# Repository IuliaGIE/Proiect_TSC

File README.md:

# DeskAssistant v15 – ESP32-C6 Smart E-Ink Device

## 🔧 Diagrama bloc

---

## 📦 Bill of Materials (BOM)

| Componentă | Link Mouser | Link Comet | Datasheet |
|------------|-------------|------------|-----------|
| ESP32-C6-WROOM-1 | [Mouser](https://www.mouser.com/ProductDetail/356-ESP32C6WRM1) | [Comet](https://www.comet.bg/en/products/44639/) | [Datasheet ESP32-C6](https://www.espressif.com/sites/default/files/documentation/esp32-c6_datasheet_en.pdf) |
| BME688 | [Mouser](https://www.mouser.com/ProductDetail/Bosch-Sensortec/BME688) | [Comet](https://www.comet.bg/en/products/43883/) | [Datasheet BME688](https://www.bosch-sensortec.com/media/boschsensortec/downloads/datasheets/bst-bme688-ds001.pdf) |
| MAX17048 | [Mouser](https://www.mouser.com/ProductDetail/Maxim-Integrated/MAX17048G+) | [Comet](https://www.comet.bg/en/products/40714/) | [Datasheet MAX17048](https://datasheets.maximintegrated.com/en/ds/MAX17048-MAX17049.pdf) |
| MCP73831 (Battery Charger) | [Mouser](https://www.mouser.com/ProductDetail/Microchip-Technology/MCP73831T-2ACIOT) | [Comet](https://www.comet.bg/en/products/43632/) | [Datasheet MCP73831](https://ww1.microchip.com/downloads/en/DeviceDoc/20001984g.pdf) |
| DS3231 RTC | [Mouser](https://www.mouser.com/ProductDetail/Maxim-Integrated/DS3231SN) | [Comet](https://www.comet.bg/en/products/38983/) | [Datasheet DS3231](https://datasheets.maximintegrated.com/en/ds/DS3231.pdf) |
| 7.5" E-Ink Display (WSH-13187) | [Mouser](https://www.mouser.com/ProductDetail/Waveshare/WSH-13187) | [Comet](https://www.comet.bg/en/products/45670/) | [Datasheet E-Ink](https://www.waveshare.com/w/upload/0/09/7.5inch-e-paper-b-specification.pdf) |
| LDO 3.3V | [Mouser](https://www.mouser.com/ProductDetail/Texas-Instruments/LP2985AIM5-33) | [Comet](https://www.comet.bg/en/products/43540/) | [Datasheet LDO](https://www.ti.com/lit/ds/symlink/lp2985.pdf) |
| SD Card Socket | [Mouser](https://www.mouser.com/ProductDetail/Amphenol/101-00594-68) | [Comet](https://www.comet.bg/en/products/37655/) | [Datasheet Socket](https://cdn.amphenol-icc.com/media/wysiwyg/files/drawing/10100594681.pdf) |
| LiPo Battery 2500mAh | [Mouser](https://www.mouser.com/ProductDetail/Adafruit/328) | [Comet](https://www.comet.bg/en/products/37491/) | [Specificații](https://cdn-shop.adafruit.com/datasheets/328.pdf) |

---

## 🧠 Funcționalitate Hardware

DeskAssistant v15 este un dispozitiv portabil cu ecran E-Ink, destinat afișării de informații de mediu, oră și nivel baterie. Este alimentat fie prin USB-C, fie dintr-o baterie LiPo de 2500 mAh.

### Flux de alimentare:
- Portul USB-C oferă 5V către MCP73831, care încarcă bateria LiPo.
- Tensiunea de 3.7V de la baterie este convertită de un LDO în 3.3V, alimentând toate componentele.
- Monitorizarea bateriei este realizată cu MAX17048.

### Senzori și afișaj:
- Temperatura, umiditatea, presiunea și compușii volatili (VOC) sunt măsurați cu senzorul BME688 prin magistrala I2C.
- RTC-ul DS3231 furnizează ora exactă, tot prin I2C.
- Afișajul E-Ink de 7.5 inch este conectat prin SPI și oferă un consum redus de energie.
- Datele pot fi salvate pe un card microSD (SPI).
- Trei butoane conectate pe GPIO sunt utilizate pentru controlul interfeței.

### Calcul estimativ consum:
- ESP32-C6: ~20mA în idle, ~200mA în Wi-Fi TX
- E-Ink: consum doar în actualizare (~26mA)
- BME688: ~2.1mA în mod activ
- RTC: ~1.5μA
- MAX17048: ~50μA
- Autonomie estimată: ~30-40 ore în regim normal, cu Wi-Fi ocazional

---

## 📌 Maparea pinilor ESP32-C6

| Componentă | Pin ESP32-C6 | Interfață | Motivare |
|------------|---------------|-----------|----------|
| E-Ink Display | GPIO4 (MOSI), GPIO5 (MISO), GPIO6 (SCK), GPIO7 (CS), GPIO8 (DC), GPIO9 (RST), GPIO10 (BUSY) | SPI | Control complet al ecranului |
| SD Card | GPIO11 (CS2) | SPI (partajat) | Acces la stocare externă |
| BME688 | GPIO18 (SDA), GPIO19 (SCL) | I2C | Măsurători ambientale |
| MAX17048 | GPIO18 (SDA), GPIO19 (SCL) | I2C | Nivel baterie |
| DS3231 RTC | GPIO18 (SDA), GPIO19 (SCL) | I2C | Ceas exact |
| Butoane | GPIO21, GPIO22, GPIO23 | GPIO IN | Control manual |
| USB-C | GPIO20 (USB D+), GPIO21 (USB D-) | USB-Serial | Flash & debug |
| LED status | GPIO2 | GPIO OUT | Indicație vizuală |

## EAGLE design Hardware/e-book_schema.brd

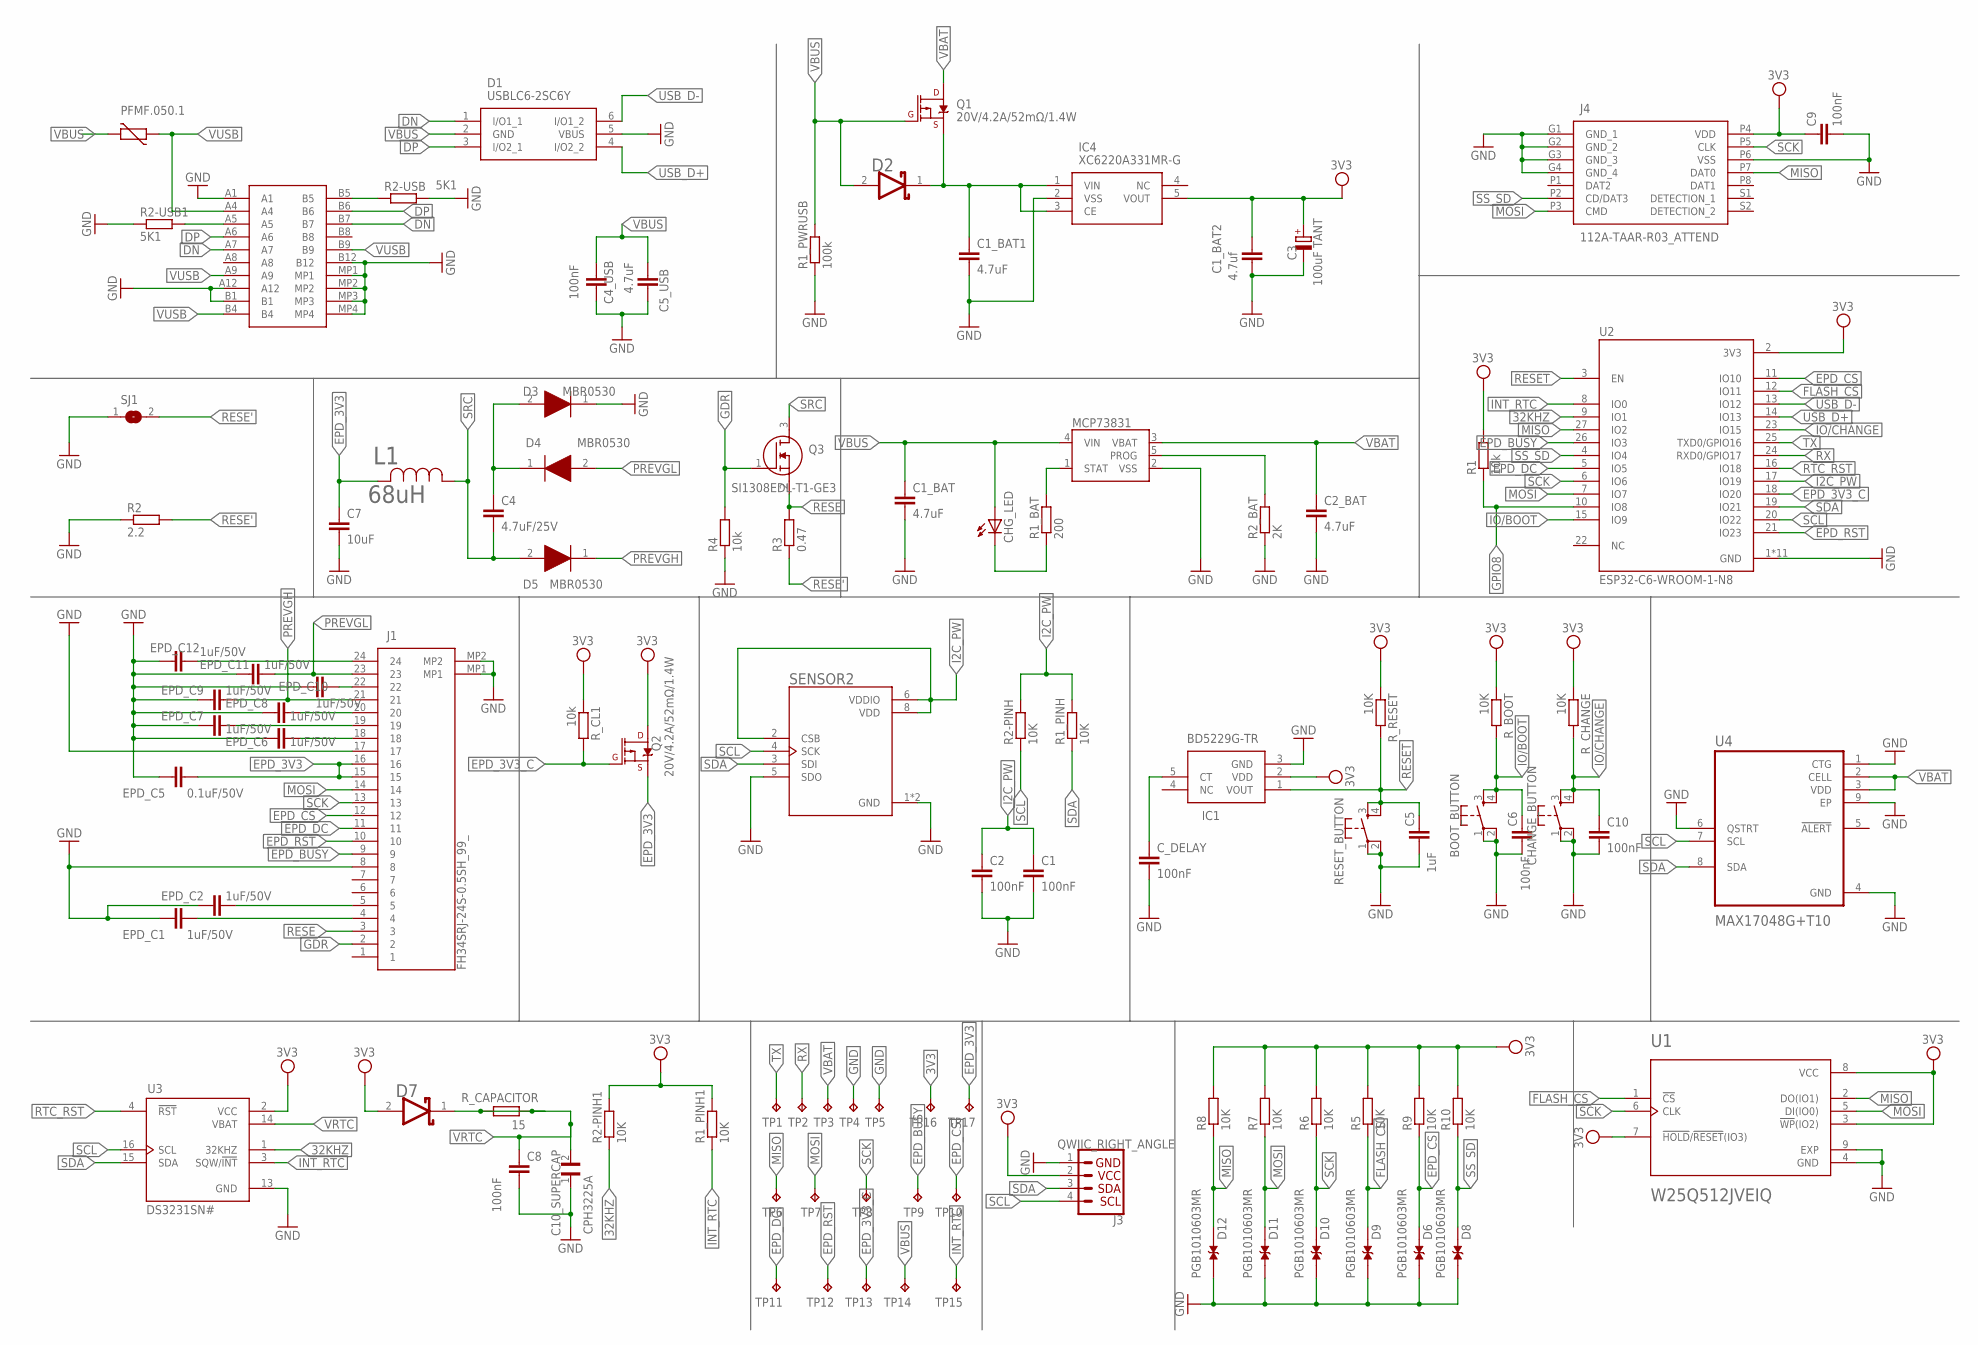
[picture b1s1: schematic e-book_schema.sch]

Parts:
BOOT_BUTTON: BUTTON_CUSYOMV1; MYBUTTON
C1, C2, C4_USB, C6, C8, C9, C10: 100nF; EAGLE-LTSPICE_C0402
C1_BAT, C1_BAT1, C2_BAT, C5_USB: 4.7uF; EAGLE-LTSPICE_C0402
C1_BAT2: 4.7uf; EAGLE-LTSPICE_C0402
C3: 100uF TANT; RCL_CT3528
C4: 4.7uF/25V; EAGLE-LTSPICE_C0402
C5: 1uF; EAGLE-LTSPICE_C0402
C7: 10uF; EAGLE-LTSPICE_C0402
C10_SUPERCAP: CPH3225A; CAPCP3225X100N
CHANGE_BUTTON: BUTTON_CUSYOMV1; MYBUTTON
CHG_LED: ADAFRUIT_LEDCHIP-LED0603; ADAFRUIT_CHIP-LED0603
C_DELAY: 100nF; EAGLE-LTSPICE_C0402
D1: USBLC6-2SC6Y; SOT95P280X145-6N
D2, D7: ESP32_WROVER_AVX---SD0805S020S1R0_AVX_SD0805S020S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; ESP32_WROVER_AVX---SD0805S020S1R0_AVX_SD0805S020S1R0_0
D3, D4, D5: MBR0530; SOD3716X135N
D6, D8, D9, D10, D11, D12: PGB1010603MR; DIOC1608X36N
EPD_C1, EPD_C2, EPD_C6, EPD_C7, EPD_C8, EPD_C9, EPD_C10, EPD_C11, EPD_C12: 1uF/50V; EAGLE-LTSPICE_C0402
EPD_C5: 0.1uF/50V; EAGLE-LTSPICE_C0402
IC1: BD5229G-TR; SOT95P280X125-5N
IC4: XC6220A331MR-G; SOT95P280X120-5N
J1: FH34SRJ-24S-0.5SH_99_; FH34SRJ24S05SH99
J2: SAMACSYS_PARTS_USB4110-GF-A; SAMACSYS_PARTS_USB4110GFA
J3: QWIIC_RIGHT_ANGLE; JST04_1MM_RA
J4: 112A-TAAR-R03_ATTEND; 112ATAARR03ATTEND
L1: 68uH; IND_4828-WE-TPC_WRE
MCP73831: ESP32_WROVER_SPARKFUN-IC-POWER_MCP73831; ESP32_WROVER_SPARKFUN-IC-POWER_SOT23-5
PFMF.050.1: ESP32C6_VARISTORCN1812; ESP32C6_VARISTOR_CT/CN1812
Q1, Q2: 20V/4.2A/52mΩ/1.4W; ESP32_WROVER_SPARKFUN-DISCRETESEMI_SOT23-3
Q3: SI1308EDL-T1-GE3; SOT65P210X110-3N
R1, R4: 10k; ESP32_WROVER_EAGLE-LTSPICE_R0402
R1_BAT: 200; ESP32_WROVER_EAGLE-LTSPICE_R0402
R1_PINH, R1_PINH1, R2-PINH, R2-PINH1, R5, R6, R7, R8, R9, R10: 10K; ESP32_WROVER_EAGLE-LTSPICE_R0402
R1_PWRUSB: 100k; ESP32_WROVER_EAGLE-LTSPICE_R0402
R2: 2.2; ESP32_WROVER_EAGLE-LTSPICE_R0402
R2-USB, R2-USB1: 5K1; ESP32_WROVER_EAGLE-LTSPICE_R0402
R2_BAT: 2K; ESP32_WROVER_EAGLE-LTSPICE_R0402
R3: 0.47; ESP32_WROVER_EAGLE-LTSPICE_R0402
RESET_BUTTON: BUTTON_CUSYOMV1; MYBUTTON
R_BOOT: 10K; ESP32_WROVER_EAGLE-LTSPICE_R0402
R_CAPACITOR: 15; ESP32_WROVER_EAGLE-LTSPICE_R0402
R_CHANGE: 10K; ESP32_WROVER_EAGLE-LTSPICE_R0402
R_CL1: 10k; ESP32_WROVER_EAGLE-LTSPICE_R0402
R_RESET: 10K; ESP32_WROVER_EAGLE-LTSPICE_R0402
SENSOR2: ESP32_WROVER_BME680_BME680; ESP32_WROVER_BME680_PSON80P300X300X100-8N
SJ1: SJ
TP1, TP2, TP3, TP4, TP5, TP6, TP7, TP8, TP9, TP10, TP11, TP12, TP13, TP14, TP15, TP16, TP17: TPTP20R; TP20R
U1: W25Q512JVEIQ; SON127P600X800X80-9N
U2: ESP32-C6-WROOM-1-N8; XCVR_ESP32-C6-WROOM-1-N8
U3: DS3231SN#; SOIC127P1032X265-16N
U4: MAX17048G+T10; SON50P200X200X80-9N

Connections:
3V3: C1_BAT2.1, C3.+, C9.1, D7.2 (ANODE), IC1.2 (VDD), IC4.5 (VOUT), J3.2, J4.P4 (VDD), Q2.3 (D), R1.2, R1_PINH1.2, R2-PINH1.2, R5.2, R6.2, R7.2, R8.2, R9.2, R10.2, R_BOOT.1, R_CHANGE.1, R_CL1.1, R_RESET.1, TP16.TP, U1.3 (!WP!(IO2)), U1.7 (!HOLD!/!RESET!(IO3)), U1.8 (VCC), U2.2 (3V3), U3.2 (VCC)
32KHZ: R2-PINH1.1, U2.9 (IO1), U3.1 (32KHZ)
DN: D1.1 (I/O1_1), J2.A7, J2.B7
DP: D1.3 (I/O2_1), J2.A6, J2.B6
EPD_3V3: C7.1, EPD_C5.1, J1.15, J1.16, L1.2, Q2.2 (S), TP17.TP
EPD_3V3_C: Q2.1 (G), R_CL1.2, TP13.TP, U2.18 (IO20)
EPD_BUSY: J1.9, TP9.TP, U2.26 (IO3)
EPD_CS: D6.2, J1.12, R9.1, TP10.TP, U2.11 (IO10)
EPD_DC: J1.11, TP11.TP, U2.5 (IO5)
EPD_RST: J1.10, TP12.TP, U2.21 (IO23)
FLASH_CS: D9.2, R5.1, U1.1 (!CS), U2.12 (IO11)
GDR: J1.2, Q3.1 (G), R4.2
GND: BOOT_BUTTON.1, BOOT_BUTTON.2, C1.2, C1_BAT.2, C1_BAT1.2, C1_BAT2.2, C2.2, C2_BAT.2, C3.-, C4_USB.2, C5.2, C5_USB.2, C6.2, C7.2, C8.2, C9.2, C10.2, C10_SUPERCAP.1, CHANGE_BUTTON.1, CHANGE_BUTTON.2, C_DELAY.2, D1.5 (VBUS), D3.1 (K), D6.1, D8.1, D9.1, D10.1, D11.1, D12.1, EPD_C1.2, EPD_C2.2, EPD_C5.2, EPD_C6.2, EPD_C7.2, EPD_C8.2, EPD_C9.2, EPD_C10.2, EPD_C11.2, EPD_C12.2, IC1.3 (GND), IC4.2 (VSS), J1.8, J1.17, J1.MP1, J1.MP2, J2.A1, J2.A12, J2.B1, J2.B12, J2.MP1, J2.MP2, J2.MP3, J2.MP4, J3.1, J4.G1 (GND_1), J4.G2 (GND_2), J4.G3 (GND_3), J4.G4 (GND_4), J4.P6 (VSS), MCP73831.2 (VSS), R1_PWRUSB.1, R2.1, R2-USB.2, R2-USB1.1, R2_BAT.1, R4.1, RESET_BUTTON.1, RESET_BUTTON.2, SENSOR2.1 (GND), SENSOR2.5 (SDO), SENSOR2.7 (GND), SJ1.1, TP4.TP, TP5.TP, U1.4 (GND), U1.9 (EXP), U2.1 (GND), U2.28 (GND), U2.29_1 (GND), U2.29_2 (GND), U2.29_3 (GND), U2.29_4 (GND), U2.29_5 (GND), U2.29_6 (GND), U2.29_7 (GND), U2.29_8 (GND), U2.29_9 (GND), U3.13 (GND), U4.1 (CTG), U4.4 (GND), U4.6 (QSTRT), U4.9 (EP)
GPIO8: R1.1, U2.10 (IO8)
I2C_PW: C1.1, C2.1, R1_PINH.2, R2-PINH.2, SENSOR2.2 (CSB), SENSOR2.6 (VDDIO), SENSOR2.8 (VDD), U2.17 (IO19)
INT_RTC: R1_PINH1.1, TP15.TP, U2.8 (IO0), U3.3 (SQW/!INT)
IO/BOOT: BOOT_BUTTON.3, BOOT_BUTTON.4, C6.1, R_BOOT.2, U2.15 (IO9)
IO/CHANGE: C10.1, CHANGE_BUTTON.3, CHANGE_BUTTON.4, R_CHANGE.2, U2.23 (IO15)
MISO: D12.2, J4.P7 (DAT0), R8.1, TP6.TP, U1.2 (DO(IO1)), U2.27 (IO2)
MOSI: D11.2, J1.14, J4.P3 (CMD), R7.1, TP7.TP, U1.5 (DI(IO0)), U2.7 (IO7)
unnamed: J2.A5, R2-USB1.2
unnamed: J2.B5, R2-USB.1
unnamed: C1_BAT1.1, D2.1 (CATHODE), IC4.1 (VIN), IC4.3 (CE), Q1.2 (S)
unnamed: EPD_C12.1, J1.24
unnamed: C4.1, D3.2 (A), D4.1 (K)
unnamed: CHG_LED.C, R1_BAT.1
unnamed: MCP73831.1 (STAT), R1_BAT.2
unnamed: MCP73831.5 (PROG), R2_BAT.2
unnamed: C_DELAY.1, IC1.5 (CT)
unnamed: EPD_C10.1, J1.22
unnamed: EPD_C8.1, J1.20
unnamed: EPD_C7.1, J1.19
unnamed: EPD_C6.1, J1.18
unnamed: EPD_C2.1, J1.5
unnamed: EPD_C1.1, J1.4
PREVGH: D5.1 (K), EPD_C9.1, J1.21
PREVGL: D4.2 (A), EPD_C11.1, J1.23
RESE: J1.3, Q3.2 (S), R3.2
RESE': R2.2, R3.1, SJ1.2
RESET: C5.1, IC1.1 (VOUT), RESET_BUTTON.3, RESET_BUTTON.4, R_RESET.2, U2.3 (EN)
RTC_RST: U2.16 (IO18), U3.4 (!RST)
RX: TP2.TP, U2.24 (RXD0/GPIO17)
SCK: D10.2, J1.13, J4.P5 (CLK), R6.1, TP8.TP, U1.6 (CLK), U2.6 (IO6)
SCL: J3.4, R2-PINH.1, SENSOR2.4 (SCK), U2.20 (IO22), U3.16 (SCL), U4.7 (SCL)
SDA: J3.3, R1_PINH.1, SENSOR2.3 (SDI), U2.19 (IO21), U3.15 (SDA), U4.8 (SDA)
SRC: C4.2, D5.2 (A), L1.1, Q3.3 (D)
SS_SD: D8.2, J4.P2 (CD/DAT3), R10.1, U2.4 (IO4)
TX: TP1.TP, U2.25 (TXD0/GPIO16)
USB_D+: D1.4 (I/O2_2), U2.14 (IO13)
USB_D-: D1.6 (I/O1_2), U2.13 (IO12)
VBAT: C2_BAT.1, MCP73831.3 (VBAT), Q1.3 (D), TP3.TP, U4.2 (CELL), U4.3 (VDD)
VBUS: C1_BAT.1, C4_USB.1, C5_USB.1, CHG_LED.A, D1.2 (GND), D2.2 (ANODE), MCP73831.4 (VIN), PFMF.050.1.2, Q1.1 (G), R1_PWRUSB.2, TP14.TP
VRTC: C8.1, C10_SUPERCAP.2, D7.1 (CATHODE), R_CAPACITOR.1, R_CAPACITOR.2, U3.14 (VBAT)
VUSB: J2.A4, J2.A9, J2.B4, J2.B9, PFMF.050.1.1

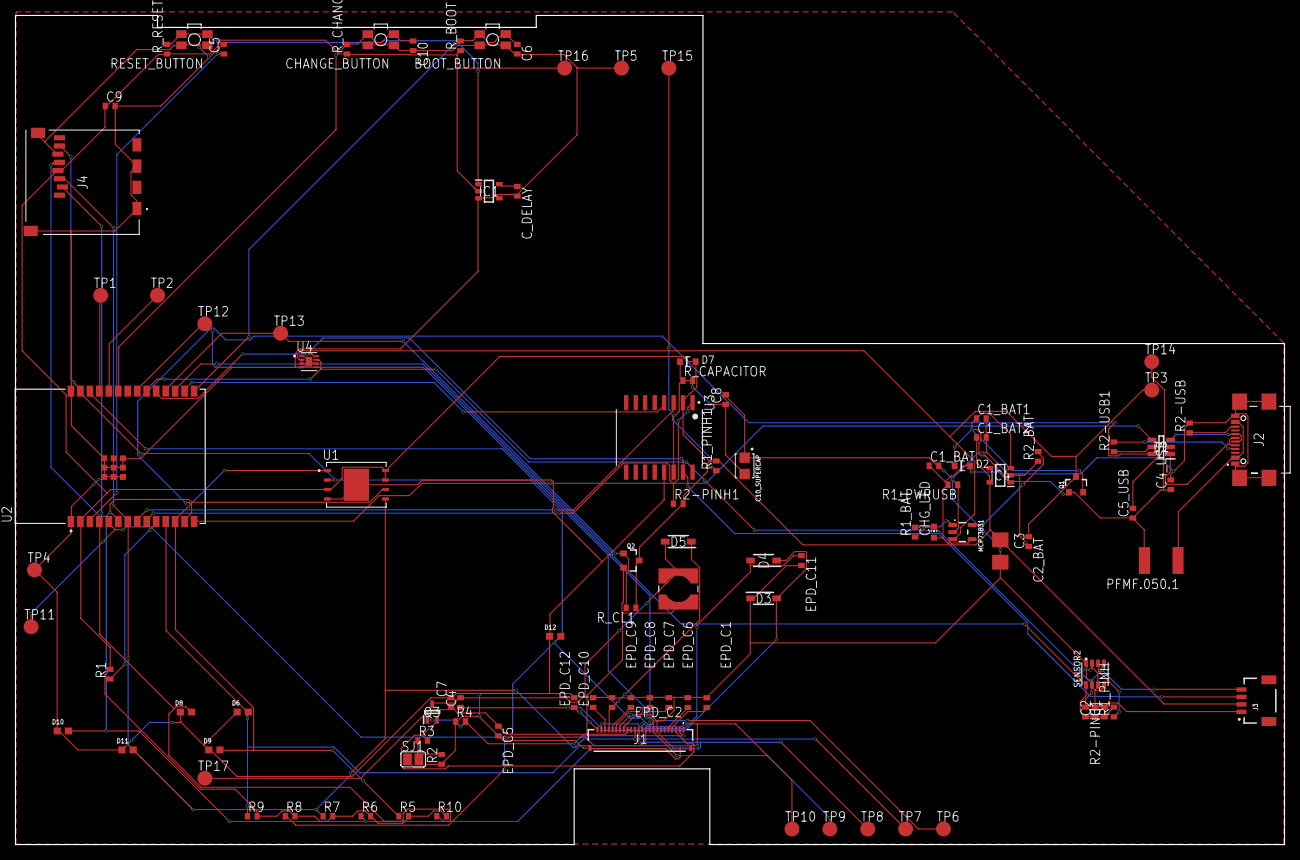
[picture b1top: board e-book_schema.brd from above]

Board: 2 copper layers, 170.2 x 111.2 mm, 103 parts (0 on the bottom side), 54 nets.

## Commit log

2025-04-06 Primul commit
2025-04-16 Actualizare conținut proiect

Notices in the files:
parts and their libraries:
COPYRIGHT: Copyright (C) 2024 Ultra Librarian. All rights reserved.
